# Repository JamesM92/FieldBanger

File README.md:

# FieldBanger_PCB
PCB to handle field programming of scare banger board

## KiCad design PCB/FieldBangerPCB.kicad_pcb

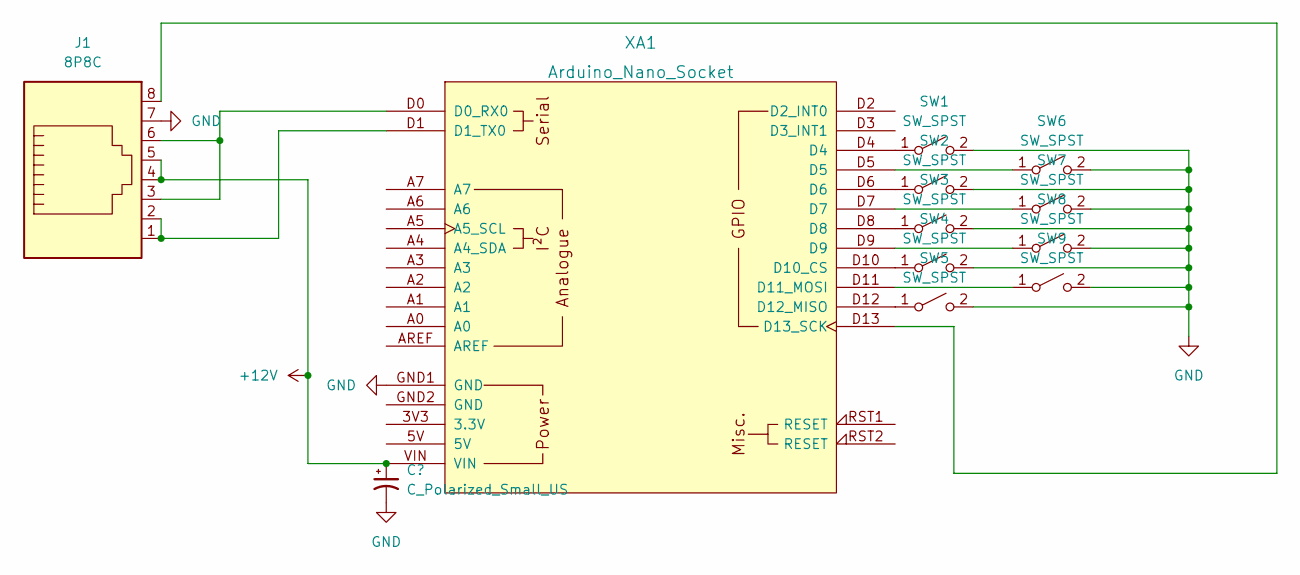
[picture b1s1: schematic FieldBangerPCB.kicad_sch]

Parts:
J1: 8P8C; RJ45_OST_PJ012-8P8CX_Vertical
SW1, SW2, SW3, SW4, SW5, SW6, SW7, SW8, SW9: SW_SPST; SW_PUSH_6mm
XA1: Arduino_Nano_Socket

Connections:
+12V: J1.4, J1.5, XA1.VIN; also elsewhere on the board
GND: J1.7, SW1.2 (B), SW2.2 (B), SW3.2 (B), SW4.2 (B), SW5.2 (B), SW6.2 (B), SW7.2 (B), SW8.2 (B), SW9.2 (B), XA1.GND1 (GND); also elsewhere on the board
unnamed: J1.1, J1.2, XA1.D1 (D1_TX0)
unnamed: J1.3, J1.6, XA1.D0 (D0_RX0)
unnamed: J1.8, XA1.D13 (D13_SCK)
unnamed: SW1.1 (A), XA1.D4
unnamed: SW2.1 (A), XA1.D6
unnamed: SW3.1 (A), XA1.D8
unnamed: SW4.1 (A), XA1.D10 (D10_CS)
unnamed: SW5.1 (A), XA1.D12 (D12_MISO)
unnamed: SW6.1 (A), XA1.D5
unnamed: SW7.1 (A), XA1.D7
unnamed: SW8.1 (A), XA1.D9
unnamed: SW9.1 (A), XA1.D11 (D11_MOSI)

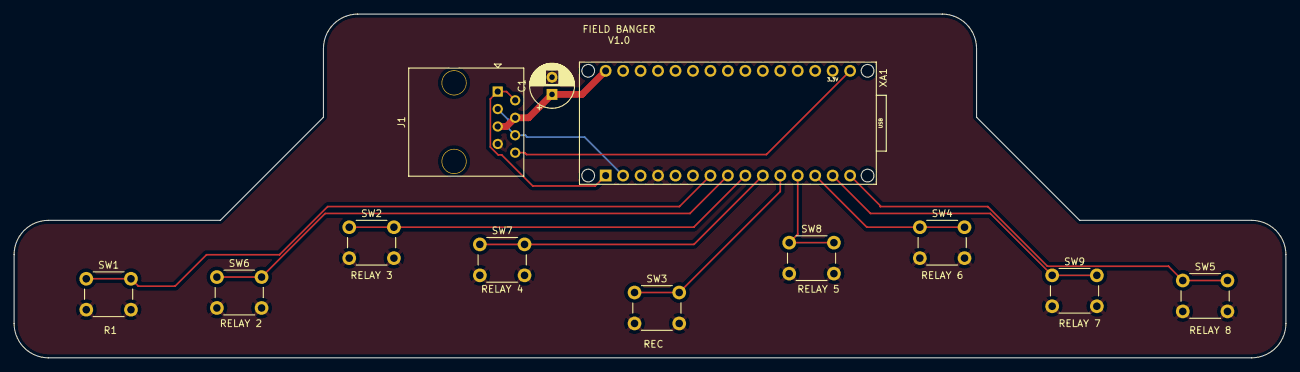
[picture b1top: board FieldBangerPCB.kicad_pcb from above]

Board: 2 copper layers, 185.0 x 50.0 mm, 12 parts (0 on the bottom side), 14 nets.

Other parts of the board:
C1: C_Polarized_Small_US; CP_Radial_D6.3mm_P2.50mm

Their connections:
+12V: C1.1; also elsewhere on the board
GND: C1.2; also elsewhere on the board

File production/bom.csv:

Designator,Footprint,Quantity,Value,LCSC Part #
XA1,Arduino_Nano_Socket,1,Arduino_Nano_Socket,
SW9,SW_PUSH_6mm,1,SW_SPST,
SW8,SW_PUSH_6mm,1,SW_SPST,
SW7,SW_PUSH_6mm,1,SW_SPST,
SW6,SW_PUSH_6mm,1,SW_SPST,
SW5,SW_PUSH_6mm,1,SW_SPST,
SW4,SW_PUSH_6mm,1,SW_SPST,
SW3,SW_PUSH_6mm,1,SW_SPST,
SW2,SW_PUSH_6mm,1,SW_SPST,
SW1,SW_PUSH_6mm,1,SW_SPST,
J1,RJ45_OST_PJ012-8P8CX_Vertical,1,8P8C,

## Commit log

2022-10-06 combined pcb with code
    combined repositories to share both pcb and code.
2022-10-09 added power cap
    added 180uF cap to power input to help with power filtering.
